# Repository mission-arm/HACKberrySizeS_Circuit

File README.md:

# HACKberrySizeS_Circuit

This repository contains circuit design of small sized [HACKberry](https://github.com/mission-arm/HACKberry).

## Licenses

The electrical circuit design of [HACKberry](https://github.com/mission-arm/HACKberry) by [Exiii](info@exiii.jp) is licensed under [Creative Commons License BY-NC-SA 4.0 International](https://creativecommons.org/licenses/by-nc-sa/4.0/).
( Please refer to chapter 3.1 in [Original HACKberry Lincense](https://github.com/mission-arm/HACKberry) for detail. )

And This electrical circuit design of small sized HACKberry ) is a derivative of HACKberry and is licensed under [Creative Commons License BY-NC-SA 4.0 International](https://creativecommons.org/licenses/by-nc-sa/4.0/) by MissionARMJapan.

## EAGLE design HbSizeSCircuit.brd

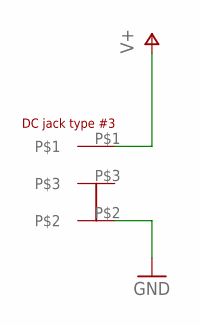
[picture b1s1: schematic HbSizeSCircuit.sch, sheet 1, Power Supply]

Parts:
U$7: HEC3110-01-010

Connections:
GND: U$7.P$2; also elsewhere on the board
V+: U$7.P$1; also elsewhere on the board

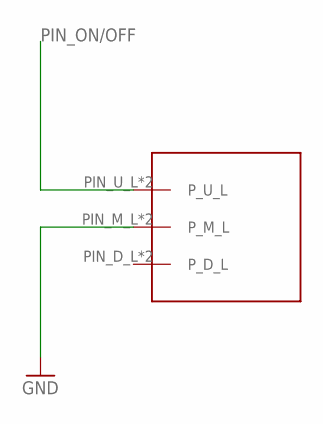
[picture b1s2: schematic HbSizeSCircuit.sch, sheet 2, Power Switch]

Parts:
U$2: IS-1250_POWERSWITCH

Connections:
GND: U$2.PIN_M_L (P_M_L), U$2.PIN_M_R (P_M_L); also elsewhere on the board
PIN_ON/OFF: U$2.PIN_U_L (P_U_L), U$2.PIN_U_R (P_U_L); also elsewhere on the board

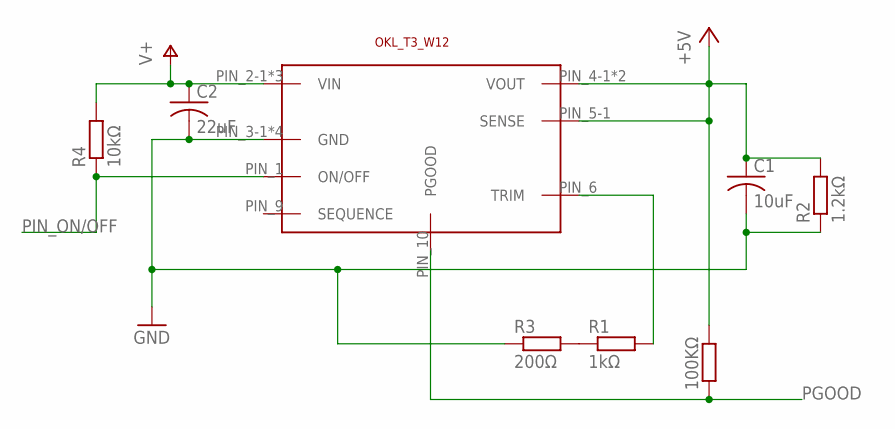
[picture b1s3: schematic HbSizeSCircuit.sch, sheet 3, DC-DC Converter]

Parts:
100KΩ: R-EU_M1206; M1206
C1: 10uF; C1206
C2: 22uF; C1206
R1: 1kΩ; M1206
R2: 1.2kΩ; M1206
R3: 200Ω; M1206
R4: 10kΩ; R1206
U$8: OKL_T3_W12

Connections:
+5V: 100KΩ.2, C1.1, R2.2, U$8.PIN_4-1 (VOUT), U$8.PIN_4-2 (VOUT), U$8.PIN_5-1 (SENSE); also elsewhere on the board
GND: C1.2, C2.2, R2.1, R3.1, U$8.PIN_3-1 (GND), U$8.PIN_3-2 (GND), U$8.PIN_3-3 (GND), U$8.PIN_7 (GND); also elsewhere on the board
unnamed: R1.2, U$8.PIN_6 (TRIM)
unnamed: R1.1, R3.2
PGOOD: 100KΩ.1, U$8.PIN_10 (PGOOD); also elsewhere on the board
PIN_ON/OFF: R4.1, U$8.PIN_1 (ON/OFF); also elsewhere on the board
V+: C2.1, R4.2, U$8.PIN_2-1 (VIN), U$8.PIN_2-2 (VIN), U$8.PIN_2-3 (VIN); also elsewhere on the board

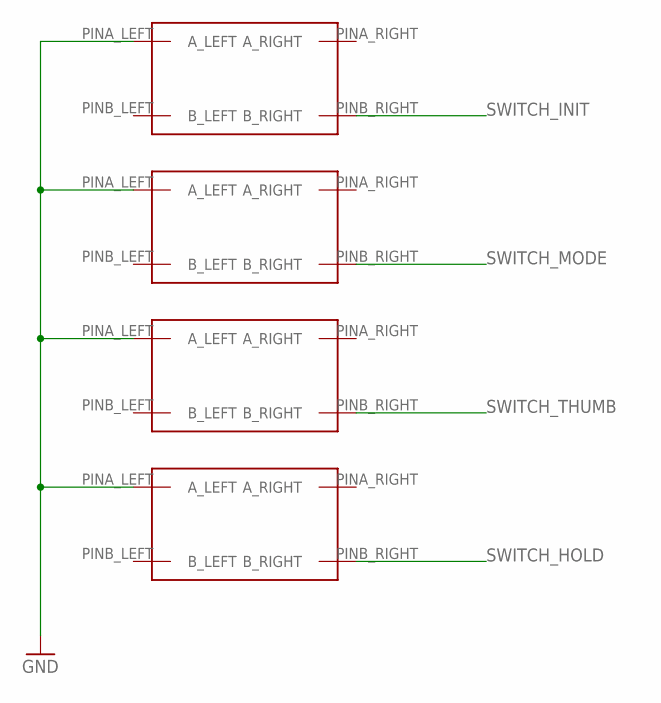
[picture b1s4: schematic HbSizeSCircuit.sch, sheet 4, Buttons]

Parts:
U$1, U$3, U$4, U$5: SKRPACE010

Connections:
GND: U$1.PINA_LEFT (A_LEFT), U$3.PINA_LEFT (A_LEFT), U$4.PINA_LEFT (A_LEFT), U$5.PINA_LEFT (A_LEFT); also elsewhere on the board
SWITCH_HOLD: U$5.PINB_RIGHT (B_RIGHT); also elsewhere on the board
SWITCH_INIT: U$1.PINB_RIGHT (B_RIGHT); also elsewhere on the board
SWITCH_MODE: U$3.PINB_RIGHT (B_RIGHT); also elsewhere on the board
SWITCH_THUMB: U$4.PINB_RIGHT (B_RIGHT); also elsewhere on the board

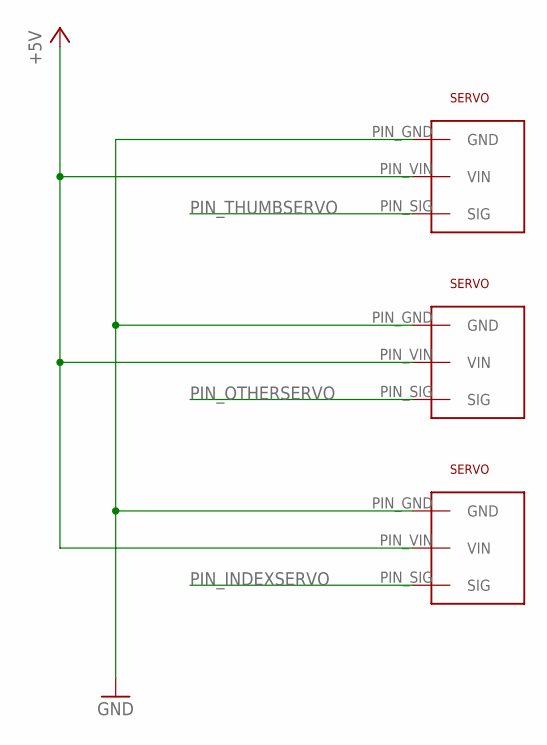
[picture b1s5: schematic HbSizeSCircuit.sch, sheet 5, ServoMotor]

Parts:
U$9, U$11, U$12: 53398-0371

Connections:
+5V: U$9.PIN_VIN (VIN), U$11.PIN_VIN (VIN), U$12.PIN_VIN (VIN); also elsewhere on the board
GND: U$9.PIN_GND (GND), U$11.PIN_GND (GND), U$12.PIN_GND (GND); also elsewhere on the board
PIN_INDEXSERVO: U$12.PIN_SIG (SIG); also elsewhere on the board
PIN_OTHERSERVO: U$11.PIN_SIG (SIG); also elsewhere on the board
PIN_THUMBSERVO: U$9.PIN_SIG (SIG); also elsewhere on the board

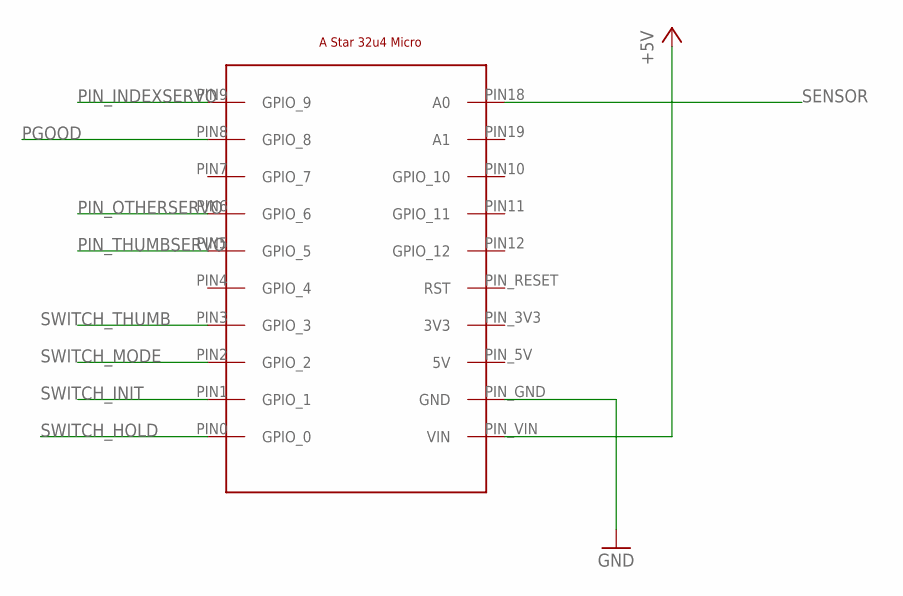
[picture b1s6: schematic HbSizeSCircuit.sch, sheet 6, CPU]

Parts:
U$6: POLOLU_A_STAR_32U4_MICRO_SMD

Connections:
+5V: U$6.PIN_VIN (VIN); also elsewhere on the board
GND: U$6.PIN_GND (GND); also elsewhere on the board
PGOOD: U$6.PIN8 (GPIO_8); also elsewhere on the board
PIN_INDEXSERVO: U$6.PIN9 (GPIO_9); also elsewhere on the board
PIN_OTHERSERVO: U$6.PIN6 (GPIO_6); also elsewhere on the board
PIN_THUMBSERVO: U$6.PIN5 (GPIO_5); also elsewhere on the board
SENSOR: U$6.PIN18 (A0); also elsewhere on the board
SWITCH_HOLD: U$6.PIN0 (GPIO_0); also elsewhere on the board
SWITCH_INIT: U$6.PIN1 (GPIO_1); also elsewhere on the board
SWITCH_MODE: U$6.PIN2 (GPIO_2); also elsewhere on the board
SWITCH_THUMB: U$6.PIN3 (GPIO_3); also elsewhere on the board

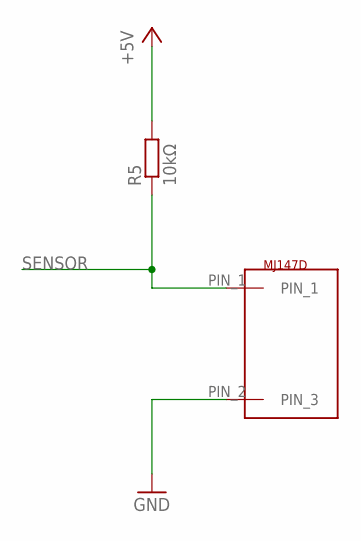
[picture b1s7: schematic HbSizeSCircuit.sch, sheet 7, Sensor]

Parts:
R5: 10kΩ; R1206
U$10: MJ147D_2PIN

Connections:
+5V: R5.2; also elsewhere on the board
GND: U$10.PIN_2 (PIN_3); also elsewhere on the board
SENSOR: R5.1, U$10.PIN_1; also elsewhere on the board

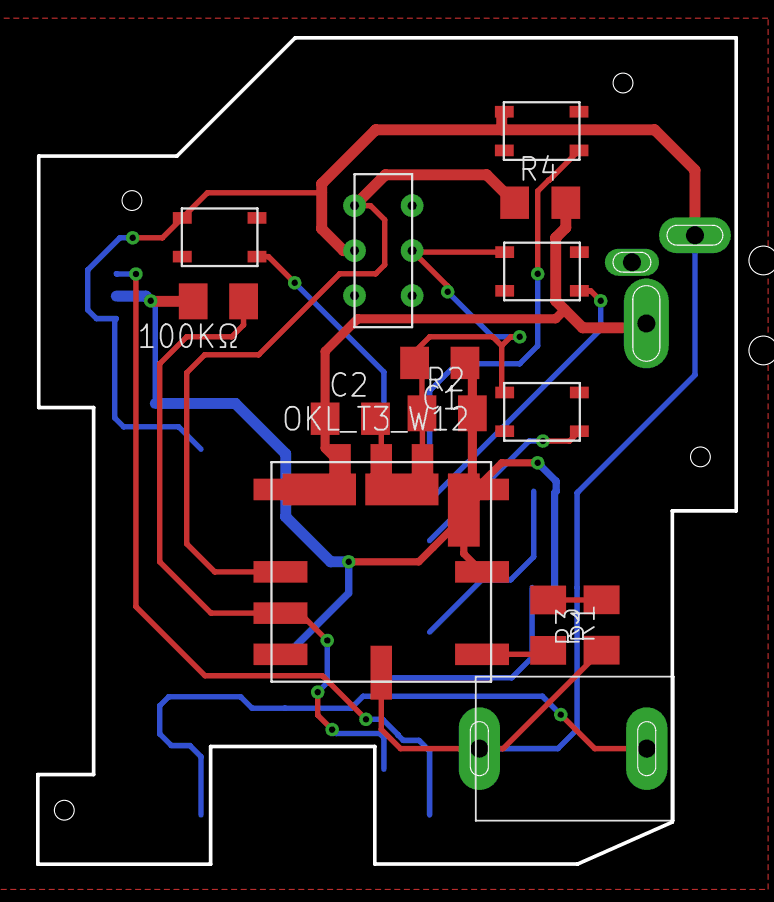
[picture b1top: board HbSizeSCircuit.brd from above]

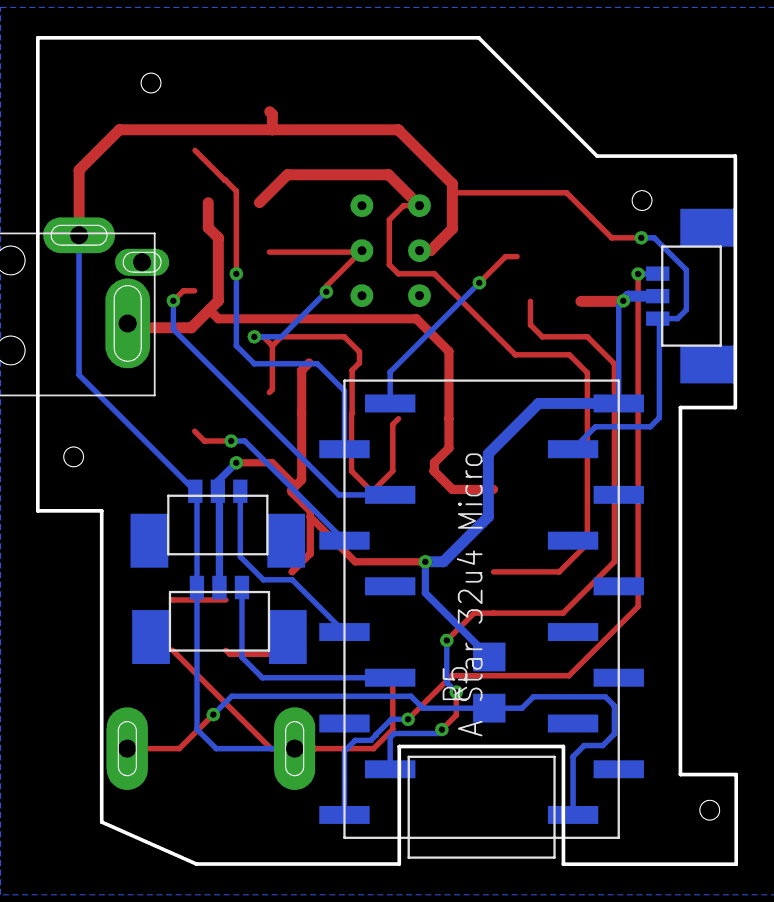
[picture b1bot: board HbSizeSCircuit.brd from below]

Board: 2 copper layers, 38.8 x 45.9 mm, 20 parts (6 on the bottom side), 15 nets.

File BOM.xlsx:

部品番号ブヒンバンゴウ | 部品名ブヒンメイ | 個数コスウ
C1 | 10uF | 1
C2 | 22uF | 1
R1 | 1kΩ | 1
R2 | 1.2kΩ | 1
R3 | 200Ω | 1
R4 | 10kΩ | 1
R5 | 10kΩ | 1
 | SKRPACE010 | 4
 | IS-1250 | 1
 | Pololu A-Star 32u4 Micro | 1
 | HEC3110-01-010 | 1
 | OKL_T/3_W12 | 1
 | 53398-0371 | 3
 | MJ147D | 1

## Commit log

2018-02-17 add schematics and board
2018-02-19 add left board file
2018-02-19 add BOM list
2018-03-06 add board layout
2018-08-19 回路図を一枚にまとめた
2019-07-19 rename artwork file
